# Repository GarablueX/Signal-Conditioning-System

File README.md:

# Real-Time Adaptive Signal Conditioning System

---

## Manufacturing Partnership

This project is sponsored by [**PCBWay**](https://www.pcbway.com/), a leading PCB manufacturing service provider.

PCBWay is supporting the fabrication of prototype hardware for this system, enabling real-world validation and testing beyond simulation. Their sponsorship demonstrates commitment to supporting engineering education and open-source development.

**Fabrication Status:** Finished

**Manufacturing Partner:** [PCBWay - Professional PCB Services](https://www.pcbway.com/)

---
### Project Gallery

*PCBs manufactured by [PCBWay](https://www.pcbway.com/) - Professional quality for precision analog circuits*

## Overview

This repository documents an engineering project focused on the design and simulation of a **Real-Time Adaptive Signal Conditioning System for Wide Dynamic Range Inputs**.

The system automatically regulates signal amplitude through level-dependent adaptive gain control, ensuring stable output behavior despite significant variations in input magnitude. While the principles draw from audio dynamic range compression, the project is framed as a generic signal conditioning and control system applicable to various engineering domains.

---

##  Technical Specifications

| Parameter | Specification |
|-----------|--------------|
| Supply Voltage | ±12V DC |
| Power Consumption | ~320mW (typical) |
| Maximum Input | 12Vpp (6V peak) |
| Frequency Response | 20Hz – 20kHz |
| Attack Time Range | 1ms – 100ms (adjustable) |
| Release Time Range | 50ms – 1.05s (adjustable) |
| Compression Ratio | 1:1 to ∞:1 (variable) |
| PCB Layers | 2-layer FR4 |
| Total Component Cost | ~$25 USD / 75 TND |

---

##  Key Features

### Core System
- **Feed-forward compression architecture** - Fast response time
- **Diode ladder voltage-controlled amplifier** - Cost-effective, low distortion
- **Precision envelope detection** - Accurate signal level monitoring
- **Adjustable threshold, attack, release, and ratio controls**
- **Input protection circuitry** - Zener clamp at 6.2V

### Optional Modules
- **Variable makeup gain amplifier** - Output level control
- **5-stage LED level indicator** - Visual feedback
- **Modular implementation** - Use only what you need

---

## Project Objectives

- Design a real-time adaptive gain control system  
- Handle wide input dynamic ranges without saturation  
- Apply control-system principles to signal conditioning  
- Validate system behavior through simulation  
- Develop manufacturable PCB implementation
- Present the design in a clear, engineering focused manner  

---

## Key Engineering Concepts

- Adaptive gain control  
- Dynamic range regulation  
- Real-time signal processing  
- Feed forward control architecture  
- Time domain system response (attack and release behavior)  

These concepts are demonstrated using standard analog test signals, such as sine waves and amplitude step inputs.

---

## Validation & Testing

System validation is conducted via circuit level simulation:

- Time-domain waveform analysis  
- Input versus output amplitude characterization  
- Gain response under varying signal levels  

Simulation is employed to isolate system behavior and verify functional correctness under controlled conditions.

---

##  Documentation

**Complete technical documentation available in `/Report.pdf`**

The comprehensive report includes:
- Theoretical background and system architecture
- Detailed circuit analysis for each functional block
- Simulation results and validation methodology
- PCB design considerations and layout strategy
- Bill of materials and cost analysis
- Power consumption analysis and thermal considerations
- Design iterations and problem-solving process

---

## PCB Implementation

Following simulation validation, the system has been designed for physical implementation:

- **PCB Design Tool:** KiCAD
- **PCB Specifications:** 2-layer FR4, standard manufacturing
- **Design Approach:** Modular layout, ground plane strategy, optimized trace routing
- **Manufacturing Partner:** [PCBWay](https://www.pcbway.com/)

The PCB design translates the validated circuit architecture into a manufacturable format suitable for prototype fabrication and testing.

**Current Status:** Gerber files generated, PCBs in production with PCBWay.

---

## Tools & Environment

- **Simulation Environment:** Proteus  
- **PCB Design:** KiCAD
- **Signal Type:** Analog test signals (audio-frequency range used for convenience)  
- **Methodology:** Design → Simulate → Analyze → Validate → Implement

---

## Project Status

**Completed:**
-  Core system design  
-  Functional simulation and validation
-  PCB layout and design
-  Manufacturing file preparation
-  PCB fabrication
-  Prototype assembly
-  

**In Progress:**
-  Physical testing and validation (scheduled)

Updates will be posted as i move on to the next steps.

---

## Acknowledgments

**Manufacturing Partner:**  
[**PCBWay**](https://www.pcbway.com/) - PCB fabrication sponsorship enabling physical prototype development and testing.

**Academic Context:**  
This project was developed as part of engineering studies at ISE'TCOM, with internship framework provided by ISET Sousse.

---

## Repository Structure

```
├── PCB-images/              # Technical documentation
├── Schematics in KiCad/          # KiCAD PCB design files
├── Schematics(for simulation)/           # Manufacturing files
├── topologys/        # Proteus simulation files
├── additional footprints & 3D models used/               # Foot prints and 3D models 
├── images/            # Schematics and renders
├── Report.pdf/
```

---

##  Contact & Collaboration

**Project Author:** Saif Abdessayed   

- **Email:** saif.abdessayed321@gmail.com
- **GitHub:** [@GarablueX](https://github.com/GarablueX)
- **LinkedIn:**[Saif Abd'Essayed](https://www.linkedin.com/in/saif-abdessayed/)

**Interested in collaborating?** Open an issue or pull request!

**Questions about the design?** Check the documentation or open a discussion.

---

**Last Updated:** April 2026  
**Version:** 1.2 - PCB fabrication Done

---
## License

This project is shared for educational and portfolio purposes only.

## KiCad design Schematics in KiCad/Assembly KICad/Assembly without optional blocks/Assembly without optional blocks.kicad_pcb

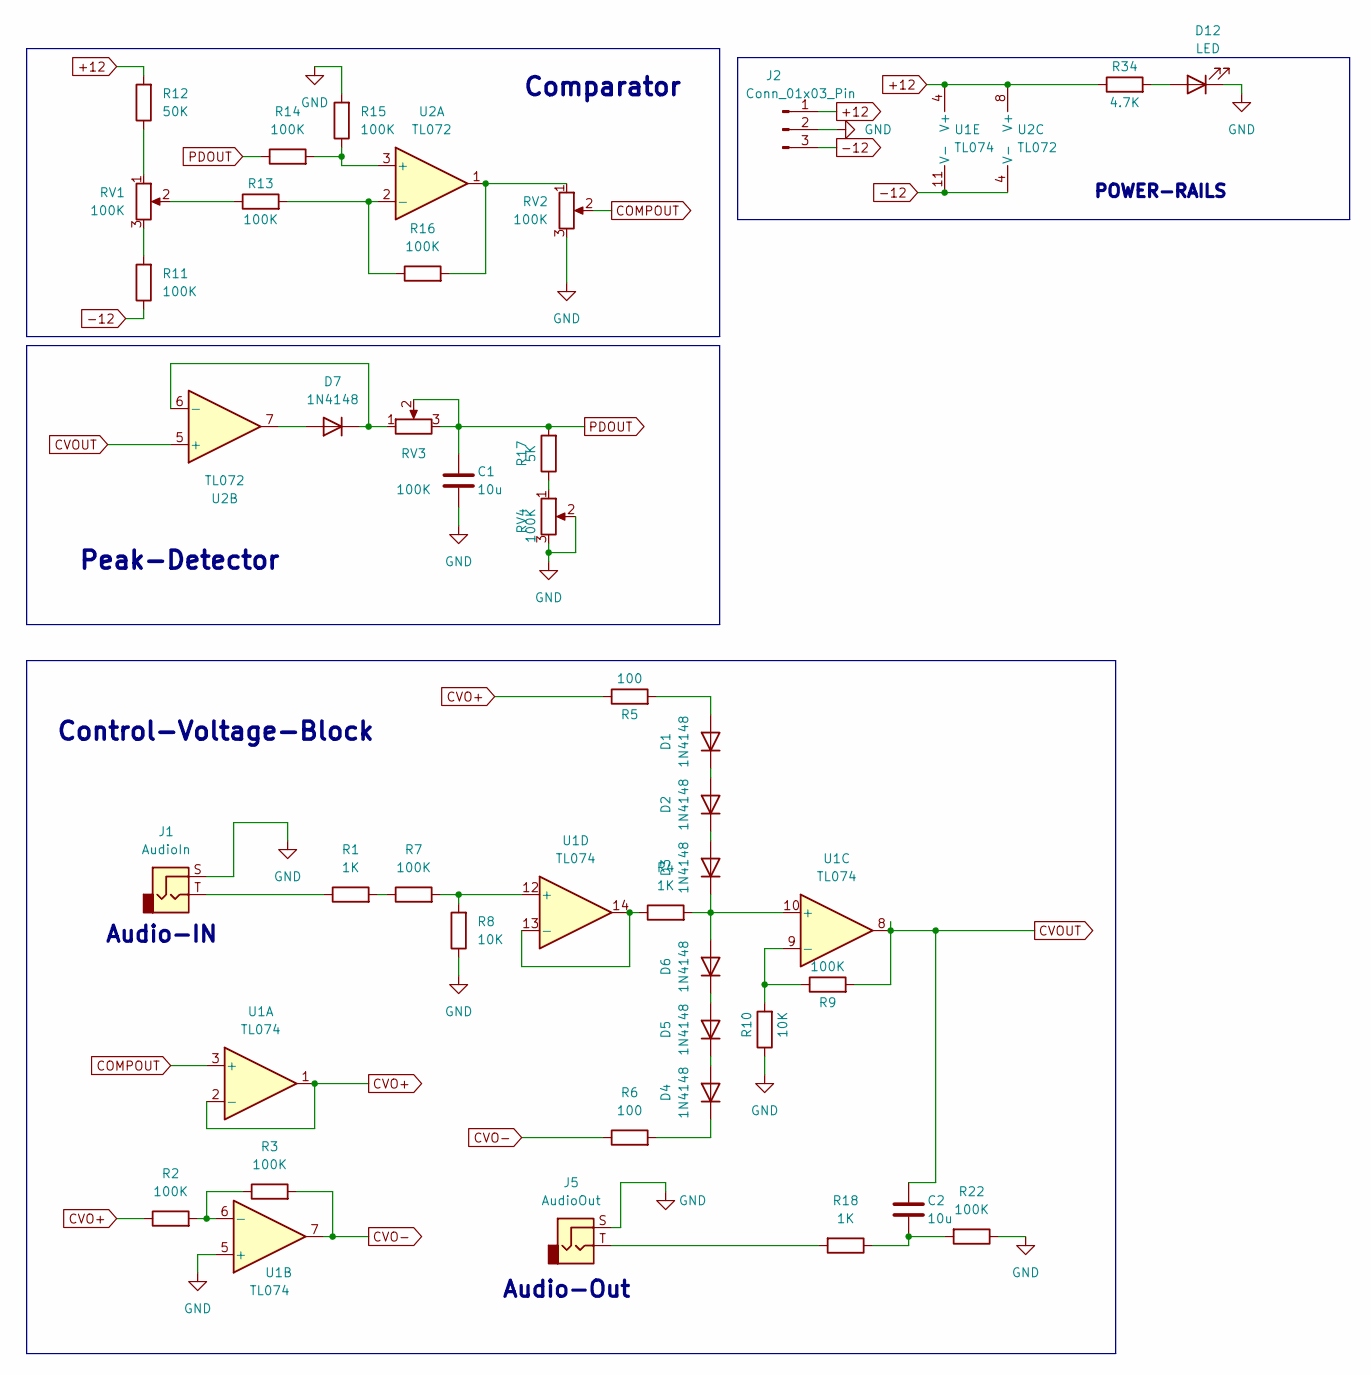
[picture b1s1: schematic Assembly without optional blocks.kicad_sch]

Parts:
C1, C2: 10u; C_Radial_D6.3mm_H5.0mm_P2.50mm
D1, D2, D3, D4, D5, D6, D7: 1N4148; D_DO-35_SOD27_P7.62mm_Horizontal
D12: LED; LED_D3.0mm_Horizontal_O1.27mm_Z2.0mm
J1: AudioIn; Jack_6.35mm_Neutrik_NJ2FD-V_Vertical
J2: Conn_01x03_Pin; PhoenixContact_MCV_1,5_3-G-5.08_1x03_P5.08mm_Vertical
J5: AudioOut; Jack_6.35mm_Neutrik_NJ2FD-V_Vertical
R1, R4, R18: 1K; R_Axial_DIN0204_L3.6mm_D1.6mm_P7.62mm_Horizontal
R2, R3, R7, R9, R11, R13, R14, R15, R16, R22: 100K; R_Axial_DIN0204_L3.6mm_D1.6mm_P7.62mm_Horizontal
R5, R6: 100; R_Axial_DIN0204_L3.6mm_D1.6mm_P7.62mm_Horizontal
R8, R10: 10K; R_Axial_DIN0204_L3.6mm_D1.6mm_P7.62mm_Horizontal
R12: 50K; R_Axial_DIN0204_L3.6mm_D1.6mm_P7.62mm_Horizontal
R17: 5K; R_Axial_DIN0204_L3.6mm_D1.6mm_P7.62mm_Horizontal
R34: 4.7K; R_Axial_DIN0204_L3.6mm_D1.6mm_P7.62mm_Horizontal
RV1, RV2, RV3, RV4: 100K; Potentiometer_Bourns_3386P_Vertical
U1: TL074; DIP-14_W7.62mm
U2: TL072; DIP-8_W7.62mm

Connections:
+12: J2.1, R12.2, R34.1, U1.4 (V+), U2.8 (V+); also elsewhere on the board
-12: J2.3, R11.1, U1.11 (V-), U2.4 (V-); also elsewhere on the board
COMPOUT: RV2.2, U1.3 (+); also elsewhere on the board
CVO+: R2.1, R5.1, U1.1, U1.2 (-)
CVO-: R3.2, R6.1, U1.7
CVOUT: C2.1, R9.2, U1.8, U2.5 (+); also elsewhere on the board
GND: C1.2, D12.1 (K), J1.S, J2.2, J5.S, R8.1, R10.1, R15.2, R22.1, RV2.3, RV4.2, RV4.3, U1.5 (+)
unnamed: C2.2, R18.1, R22.2
unnamed: D1.2 (A), R5.2
unnamed: D1.1 (K), D2.2 (A)
unnamed: D2.1 (K), D3.2 (A)
unnamed: D3.1 (K), D6.2 (A), R4.2, U1.10 (+)
unnamed: D4.2 (A), D5.1 (K)
unnamed: D4.1 (K), R6.2
unnamed: D5.2 (A), D6.1 (K)
unnamed: D7.2 (A), U2.7
unnamed: D7.1 (K), RV3.1, U2.6 (-)
unnamed: D12.2 (A), R34.2
unnamed: J1.T, R1.1
unnamed: J5.T, R18.2
unnamed: R1.2, R7.1
unnamed: R11.2, RV1.3
unnamed: R12.1, RV1.1
unnamed: R13.1, RV1.2
unnamed: R16.2, RV2.1, U2.1
unnamed: R17.1, RV4.1
unnamed: R2.2, R3.1, U1.6 (-)
unnamed: R9.1, R10.2, U1.9 (-)
unnamed: R7.2, R8.2, U1.12 (+)
unnamed: R4.1, U1.13 (-), U1.14
unnamed: R14.2, R15.1, U2.3 (+)
unnamed: R13.2, R16.1, U2.2 (-)
PDOUT: C1.1, R14.1, R17.2, RV3.2, RV3.3

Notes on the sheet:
Audio-IN
Control-Voltage-Block
Peak-Detector
POWER-RAILS
Comparator
Audio-Out

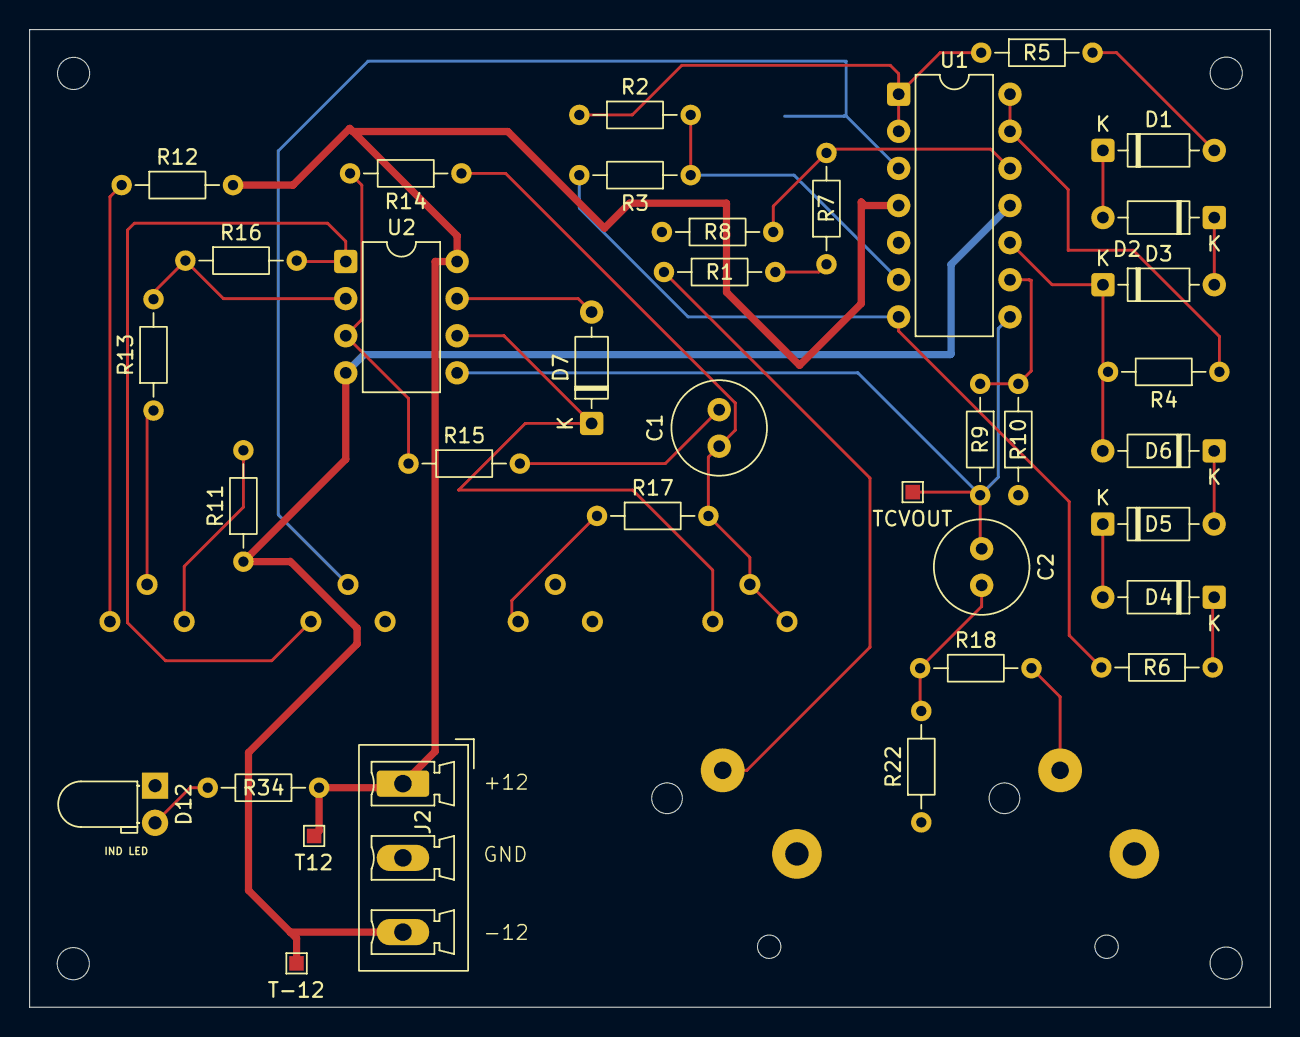
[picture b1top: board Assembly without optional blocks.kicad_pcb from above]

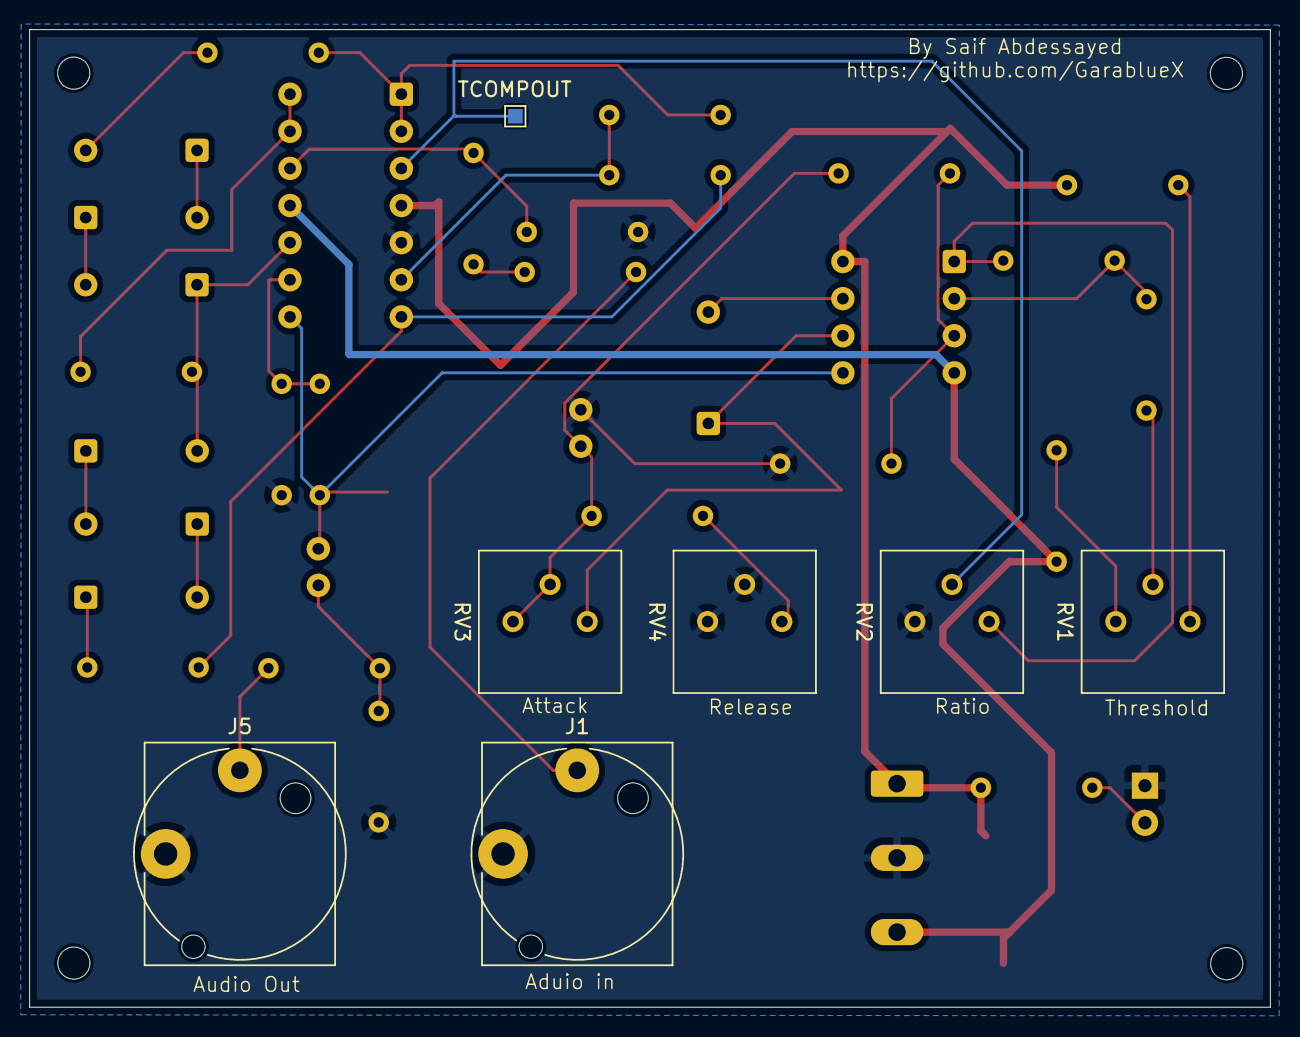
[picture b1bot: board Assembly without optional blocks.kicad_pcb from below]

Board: 2 copper layers, 84.9 x 66.9 mm, 43 parts (7 on the bottom side), 33 nets.

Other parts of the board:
T12: TestPoint_Pad_1.0x1.0mm
T-12: TestPoint_Pad_1.0x1.0mm
TCOMPOUT: TestPoint_Pad_1.0x1.0mm
TCVOUT: TestPoint_Pad_1.0x1.0mm

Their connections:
+12: T12.1; also elsewhere on the board
-12: T-12.1; also elsewhere on the board
COMPOUT: TCOMPOUT.1; also elsewhere on the board
CVOUT: TCVOUT.1; also elsewhere on the board

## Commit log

2025-12-29 Core concept & Implementation of the Voltage Control block
2025-12-29 optimizing and verifying VC block
2025-12-29 Optimizing Circuit
2025-12-29 Adding the Peak detection block
2025-12-30 Added simulations as well as some modifications on the VC block
2025-12-30 Fixing the Peak detector , adding some simulations and updating the Rapport
2025-12-31 Implementing the Assembly , making the Comparator block , Updating the Rapport
2026-01-02 Optimisation
2026-01-05 adding attack and release and ratio
    adding attack ,ratio and release knobs as well explaining them in the rapport and providing the schematics for them,
    did some debugging and testing
2026-01-06 Adding Gain control and Amplification to the system , Also updating the Rapport
2026-01-07 Adding The LED follower block and Updating the rapport
2026-01-09 Adding input Clamping & Updating the rapport
2026-01-10 Adding Kicad schematics
2026-01-10 Kicad schematics & Pics
2026-01-11 Adding schematics on Kicad as well as adding some details
    -updated schematics
    -updated footprints
    -updated 3D models
2026-01-11 Power analysis & Updating The Rapport
    full power analysis
    full schematics on kicad
    PICS for each block
    small adjustments in the schematics
2026-01-12 Starting The PCB Layout
2026-01-13 Updating Rapport
2026-01-14 Starting the pcb layout and routing process
2026-01-15 adding the first layouts and 3d views
2026-01-16 Updating the Rapport
2026-01-16 Update rapport
2026-01-18 Files for Assembly
2026-01-28 Adding BOM for manifacturing
2026-01-28 adding BOM for manif
2026-03-03 Adding needed photos
2026-03-03 [ImgBot] Optimize images
    *Total -- 1,504.37kb -> 1,244.13kb (17.3%)
    /images/image12.png -- 28.17kb -> 9.37kb (66.73%)
    /images/image16.png -- 10.10kb -> 3.55kb (64.82%)
    /images/image8.png -- 19.78kb -> 7.94kb (59.87%)
    /images/image6.png -- 7.22kb -> 3.27kb (54.65%)
    /images/image23.png -- 32.09kb -> 15.85kb (50.61%)
2026-03-03 Enhance README with project details and specifications
    Added manufacturing partnership details and technical specifications for the Real-Time Adaptive Signal Conditioning System. Updated project status and acknowledgments sections.
2026-03-03 Adding 3D View Pics
2026-03-14 Adjusting Files
2026-04-16 PCB/Assembly
2026-04-16 Updating photos
2026-04-16 Assmebly

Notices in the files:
README.md:
License: Educational
